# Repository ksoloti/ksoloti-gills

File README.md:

# ksoloti-gills
# CAD project and Gerbers for Ksoloti Gills v0.6

# Kicad 9.0!

## This is just the Gills unit (and CV expander) and will not work without a Ksoloti Core plugged in.

# Gills PCB
`Gerbers`, `BOM` and `CPL` files for the PCB are in the subfolder [/jlcpcb/production_files](https://github.com/ksoloti/ksoloti-gills/tree/main/jlcpcb/production_files)

Schematics are [here](https://github.com/ksoloti/ksoloti-gills/blob/main/ksoloti-gills_v06.pdf)

Human-readable BOM with notes and links is [here](https://github.com/ksoloti/ksoloti-gills/blob/main/ksoloti-gills_v06_bom.xlsx)

# Gills Enclosure Panels

`Gerbers` for the enclosure panels are in the subfolder [/ksoloti-gills_panel/jlcpcb/production_files](https://github.com/ksoloti/ksoloti-gills/tree/main/ksoloti-gills_panel/jlcpcb/production_files)
Although the Kicad project includes all panels, there is one gerber zip per panel: top, bottom, left, right, front, rear. If you have made edits and want to update the Gerbers, you will need to create separate Gerbers by pasting each relevant single panel in a temporary PCBNew window and `File->Plot...` it from there. Or so.
Note that there are two `ksoloti-gills-panel-top-*.zip`, one for black color, one for white. The silkscreens differ.

# Gills CV Expander PCB
`Gerbers`, `BOM` and `CPL` files for the CV Expander PCB are in the subfolder [/ksoloti-gills-cv-expander/jlcpcb/production_files](https://github.com/ksoloti/ksoloti-gills/tree/main/jlcpcb/production_files)

CV Expander Schematics are [here](https://github.com/ksoloti/ksoloti-gills/blob/main/ksoloti-gills-cv-expander/ksoloti-gills-cv-expander_v03.pdf)

BOM parts required for CV Expander are included in the main BOM (xlsx) above.

## About Licensing and Sharing 

This hardware design is shared under the "Creative Commons Attribution 4.0 International Public License" (CC BY 4.0).
This means you can use this design for almost anything, including commercial projects. You are totally free to reproduce, share, and modify it.

Because this is a physical hardware project, we ask for two small favours to keep the attribution clear:
- Keep the attribution text "CC BY 4.0 Ksoloti" on the silkscreen layer.
- If you make any significant edits and share your modified version, please note what modifications you've made. Do add something like "edit by <yourname>" if you like!

The full, official legal text is available in the `LICENSE` file in this repository. Happy hacking!

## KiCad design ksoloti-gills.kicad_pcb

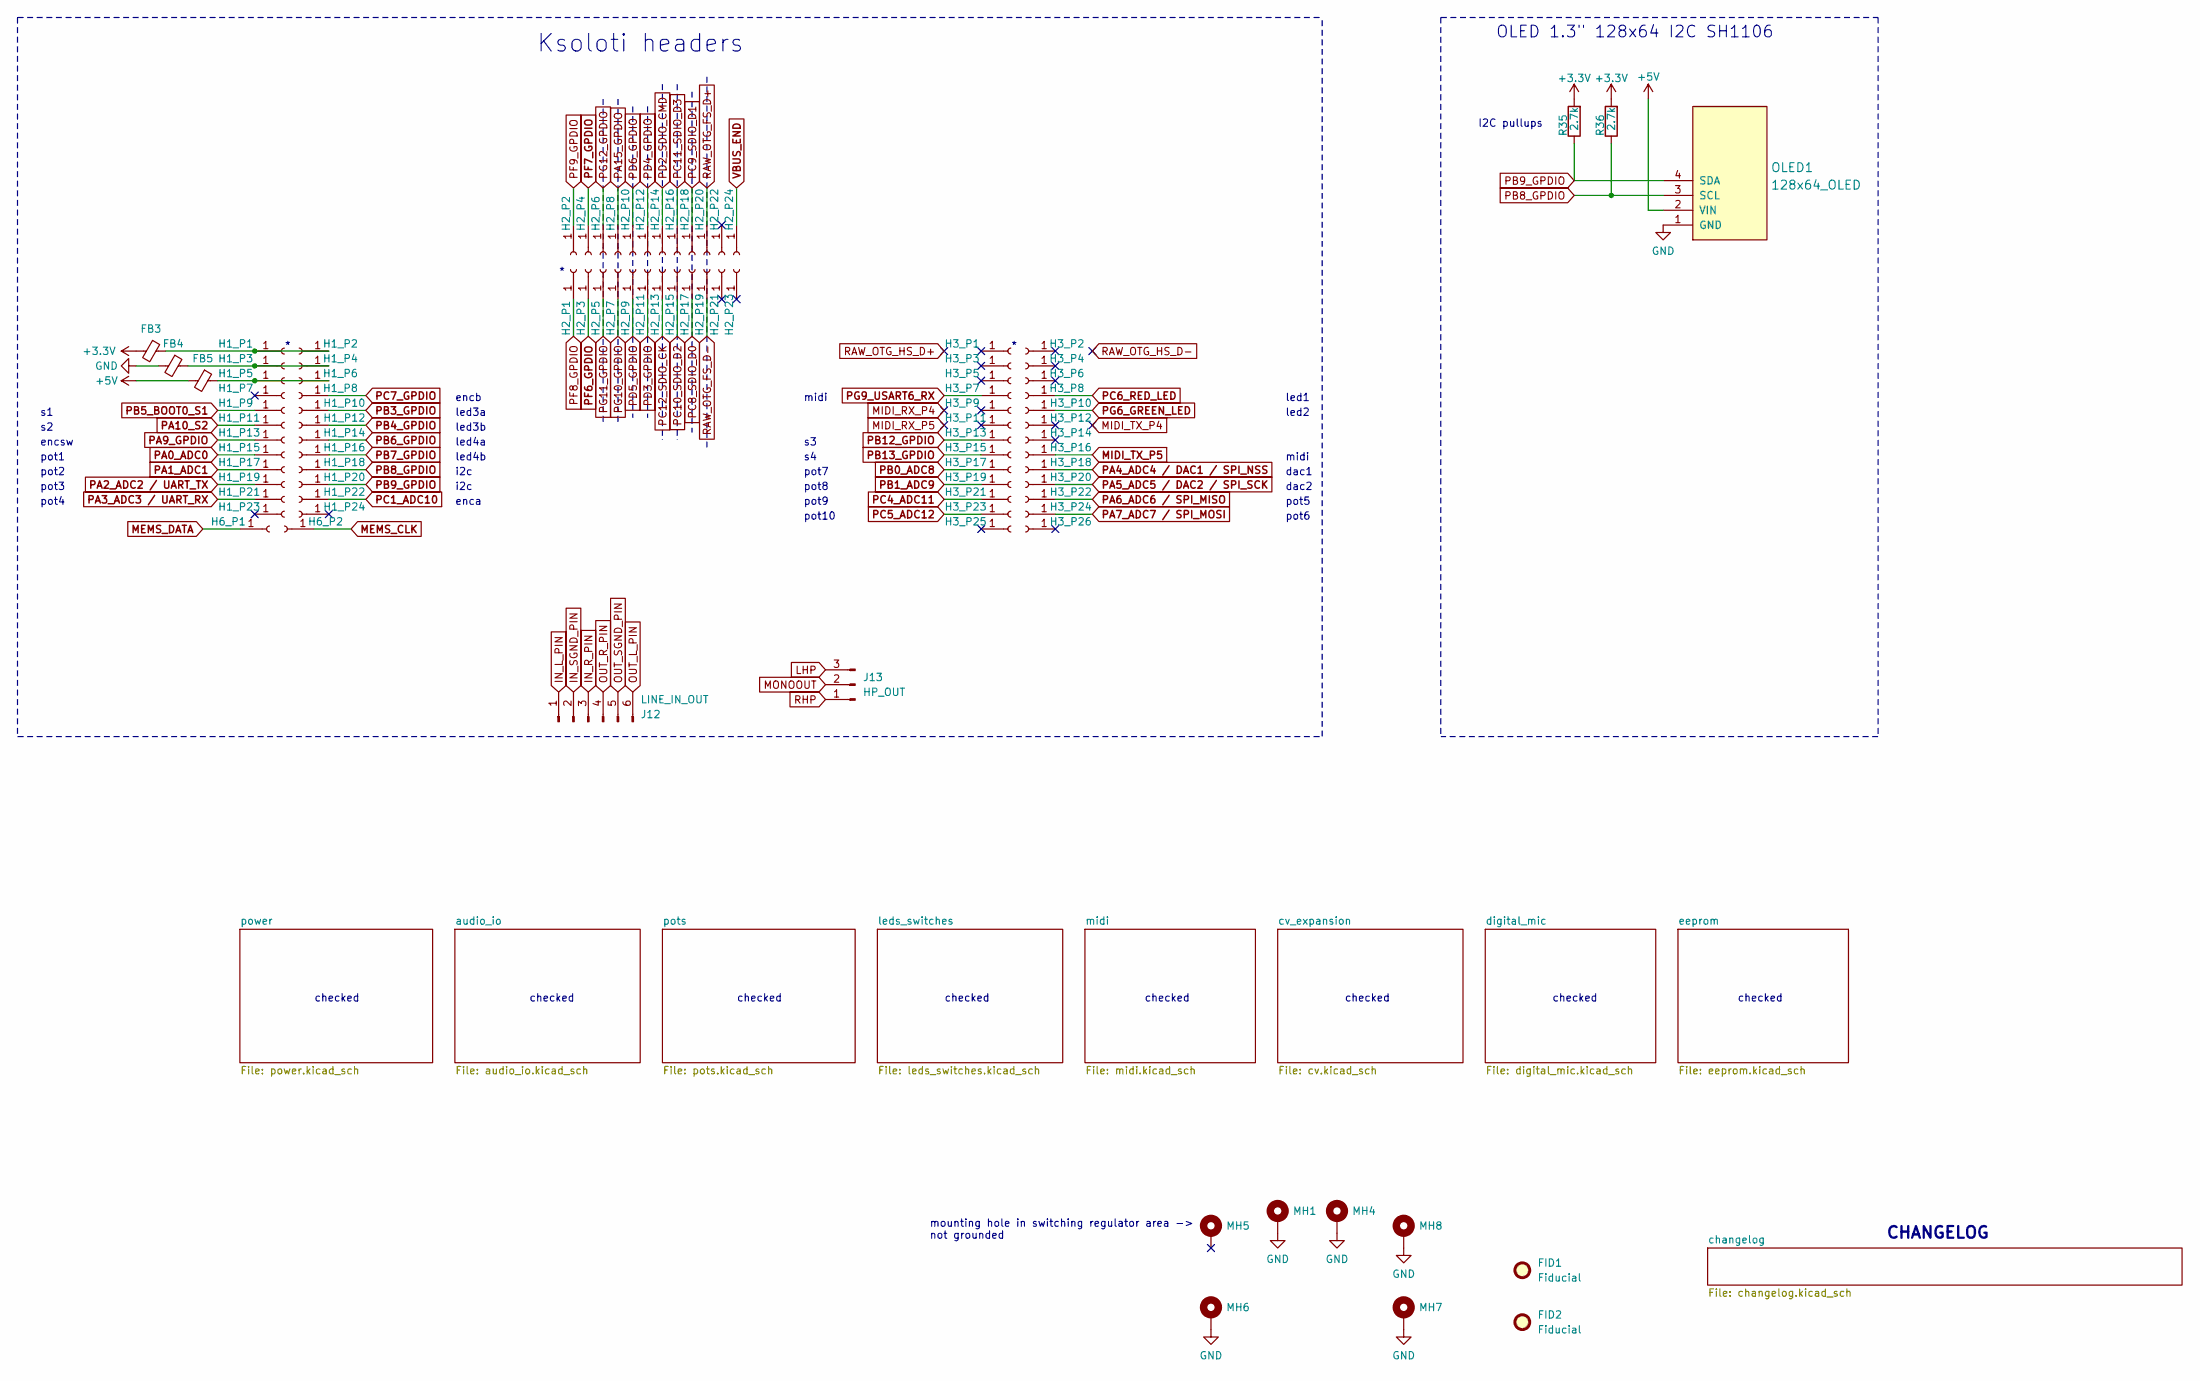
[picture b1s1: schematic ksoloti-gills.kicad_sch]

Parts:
FB3, FB4, FB5: 100 ohm @ 100 Mhz; R_1206_3216Metric
FID1, FID2: Fiducial; jlc_tooling_hole
H1_P1, H2_P1, H3_P1: Conn_01x01_Female; PinSocket_1x01_P2.54mm_Vertical_smcrt_sqr
H1_P2, H1_P3, H1_P4, H1_P5, H1_P6, H1_P7, H1_P8, H1_P9, H1_P10, H1_P11, H1_P12, H1_P13, H1_P14, H1_P15, H1_P16, H1_P17, H1_P18, H1_P19, H1_P20, H1_P21, H1_P22, H1_P23, H1_P24, H2_P2, H2_P3, H2_P4, H2_P21, H2_P22, H2_P23, H2_P24, H3_P2, H3_P3, H3_P4, H3_P5, H3_P6, H3_P7, H3_P8, H3_P9, H3_P10, H3_P11, H3_P12, H3_P13, H3_P14, H3_P15, H3_P16, H3_P17, H3_P18, H3_P19, H3_P20, H3_P21, H3_P22, H3_P23, H3_P24: Conn_01x01_Female; PinSocket_1x01_P2.54mm_Vertical_smcrt_round
H2_P5, H2_P6, H2_P7, H2_P8, H2_P9, H2_P10, H2_P11, H2_P12, H2_P13, H2_P14, H2_P15, H2_P16, H2_P17, H2_P18, H2_P19, H2_P20, H3_P25, H3_P26: Conn_01x01_Female; PinHeader_1x01_P2.54mm_Vertical_smcrt_round
H6_P1: DMIC_DAT; PinSocket_1x01_P2.54mm_Vertical_smcrt_round
H6_P2: DMIC_CLK; PinSocket_1x01_P2.54mm_Vertical_smcrt_round
J12: LINE_IN_OUT; PinSocket_1x06_P2.54mm_Vertical
J13: HP_OUT; PinSocket_1x03_P2.54mm_Vertical
MH1, MH4, MH5, MH6, MH7, MH8: MountingHole; MountingHole_3.2mm_M3_Pad_Via_tight
OLED1: 128x64_OLED; 128x64OLED_1_3in
R35, R36: 2.7k; R_0603_1608Metric

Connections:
+3.3V: FB3.2, R35.2, R36.2; also elsewhere on the board
+5V: FB5.2, OLED1.2 (VIN); also elsewhere on the board
GND: FB4.2, MH1.1, MH4.1, MH6.1, MH7.1, MH8.1, OLED1.1 (GND); also elsewhere on the board
IN_L_PIN: J12.1; also elsewhere on the board
IN_R_PIN: J12.3; also elsewhere on the board
IN_SGND_PIN: J12.2; also elsewhere on the board
LHP: J13.3; also elsewhere on the board
MEMS_CLK: H6_P2.1; also elsewhere on the board
MEMS_DATA: H6_P1.1; also elsewhere on the board
MIDI_TX_P5: H3_P16.1; also elsewhere on the board
MONOOUT: J13.2; also elsewhere on the board
unnamed: FB3.1, H1_P1.1, H1_P2.1
unnamed: FB4.1, H1_P3.1, H1_P4.1
unnamed: FB5.1, H1_P5.1, H1_P6.1
OUT_L_PIN: J12.6; also elsewhere on the board
OUT_R_PIN: J12.4; also elsewhere on the board
OUT_SGND_PIN: J12.5; also elsewhere on the board
PA0_ADC0: H1_P15.1; also elsewhere on the board
PA1_ADC1: H1_P17.1; also elsewhere on the board
PA2_ADC2 / UART_TX: H1_P19.1; also elsewhere on the board
PA3_ADC3 / UART_RX: H1_P21.1; also elsewhere on the board
PA4_ADC4 / DAC1 / SPI_NSS: H3_P18.1; also elsewhere on the board
PA5_ADC5 / DAC2 / SPI_SCK: H3_P20.1; also elsewhere on the board
PA6_ADC6 / SPI_MISO: H3_P22.1; also elsewhere on the board
PA7_ADC7 / SPI_MOSI: H3_P24.1; also elsewhere on the board
PA9_GPDIO: H1_P13.1; also elsewhere on the board
PA10_S2: H1_P11.1; also elsewhere on the board
PB0_ADC8: H3_P17.1; also elsewhere on the board
PB1_ADC9: H3_P19.1; also elsewhere on the board
PB3_GPDIO: H1_P10.1; also elsewhere on the board
PB4_GPDIO: H1_P12.1; also elsewhere on the board
PB5_BOOT0_S1: H1_P9.1; also elsewhere on the board
PB6_GPDIO: H1_P14.1; also elsewhere on the board
PB7_GPDIO: H1_P16.1; also elsewhere on the board
PB8_GPDIO: H1_P18.1, OLED1.3 (SCL), R36.1; also elsewhere on the board
PB9_GPDIO: H1_P20.1, OLED1.4 (SDA), R35.1; also elsewhere on the board
PB12_GPDIO: H3_P13.1; also elsewhere on the board
PB13_GPDIO: H3_P15.1; also elsewhere on the board
PC1_ADC10: H1_P22.1; also elsewhere on the board
PC4_ADC11: H3_P21.1; also elsewhere on the board
PC5_ADC12: H3_P23.1; also elsewhere on the board
PC6_RED_LED: H3_P8.1; also elsewhere on the board
PC7_GPDIO: H1_P8.1; also elsewhere on the board
PF6_GPDIO: H2_P3.1; also elsewhere on the board
PF7_GPDIO: H2_P4.1; also elsewhere on the board
PF8_GPDIO: H2_P1.1
PF9_GPDIO: H2_P2.1
PG6_GREEN_LED: H3_P10.1; also elsewhere on the board
PG9_USART6_RX: H3_P7.1; also elsewhere on the board
RHP: J13.1; also elsewhere on the board
VBUS_END: H2_P24.1; also elsewhere on the board

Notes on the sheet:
checked
dac2
i2c
led2
led3a
led3b
mounting hole in switching regulator area -> not grounded
led1
encb
pot10
encsw
midi
pot5
pot1
OLED 1.3" 128x64 I2C SH1106
pot8
I2C pullups
Ksoloti headers
pot2
CHANGELOG
led4b
pot7
led4a
pot6
enca
pot3
pot4
pot9
dac1

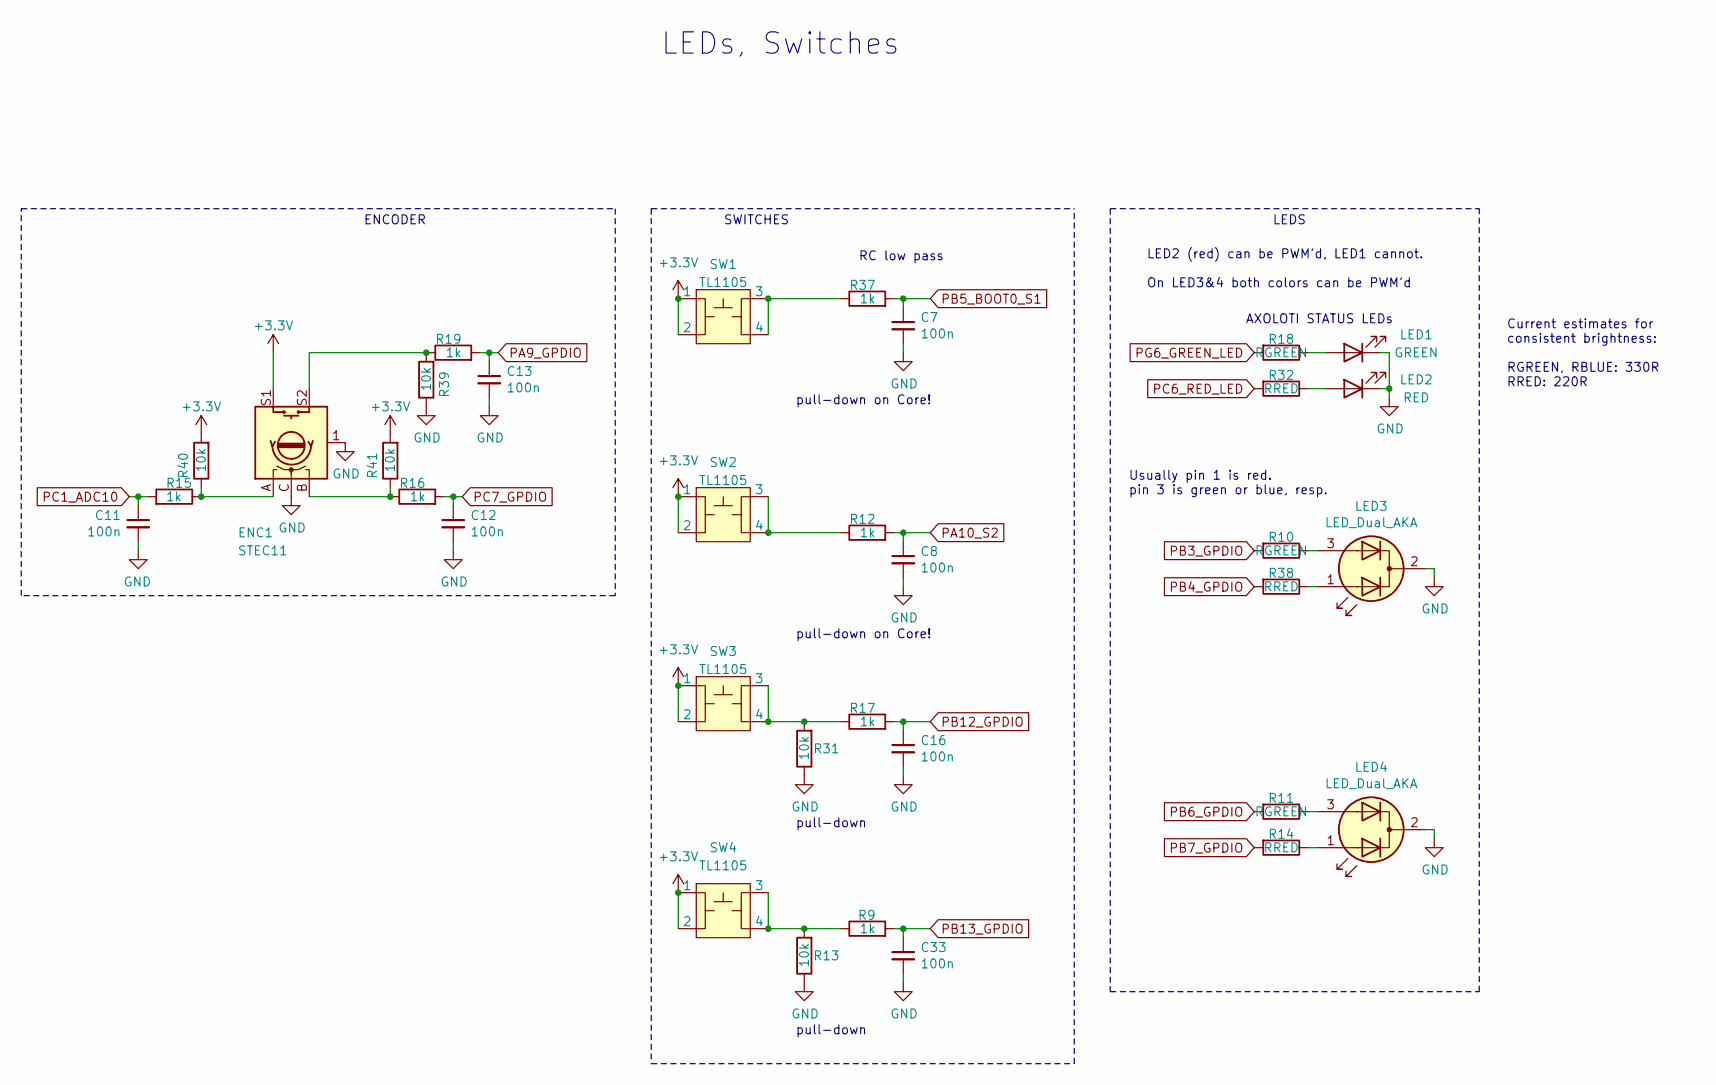
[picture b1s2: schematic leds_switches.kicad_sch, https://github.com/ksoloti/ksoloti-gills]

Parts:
C7, C8, C11, C12, C13, C16, C33: 100n; C_0603_1608Metric
ENC1: STEC11; ALPS_STEC12E08
LED1: GREEN; LED_D3.0mm_marked
LED2: RED; LED_D3.0mm_marked
LED3, LED4: LED_Dual_AKA; LED_D3.0mm-3_marked
R9, R12, R15, R16, R17, R19, R37: 1k; R_0603_1608Metric
R10, R11, R18: RGREEN; R_0805_2012Metric
R13, R31, R39, R40, R41: 10k; R_0603_1608Metric
R14, R32, R38: RRED; R_0805_2012Metric
SW1, SW2, SW3, SW4: TL1105; TL1105T

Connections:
+3.3V: ENC1.S1, R40.2, R41.2, SW1.1, SW1.2, SW2.1, SW2.2, SW3.1, SW3.2, SW4.1, SW4.2; also elsewhere on the board
GND: C7.2, C8.2, C11.2, C12.2, C13.2, C16.2, C33.2, ENC1.1, ENC1.C, LED1.1 (K), LED2.1 (K), LED3.2 (K), LED4.2 (K), R13.1, R31.1, R39.1; also elsewhere on the board
unnamed: ENC1.A, R15.1, R40.1
unnamed: ENC1.B, R16.1, R41.1
unnamed: ENC1.S2, R19.1, R39.2
unnamed: LED1.2 (A), R18.1
unnamed: LED2.2 (A), R32.1
unnamed: LED3.1 (A1), R38.1
unnamed: LED3.3 (A2), R10.1
unnamed: LED4.1 (A1), R14.1
unnamed: LED4.3 (A2), R11.1
unnamed: R12.1, SW2.3, SW2.4
unnamed: R9.1, R13.2, SW4.3, SW4.4
unnamed: R17.1, R31.2, SW3.3, SW3.4
unnamed: R37.1, SW1.3, SW1.4
PA9_GPDIO: C13.1, R19.2; also elsewhere on the board
PA10_S2: C8.1, R12.2; also elsewhere on the board
PB3_GPDIO: R10.2; also elsewhere on the board
PB4_GPDIO: R38.2; also elsewhere on the board
PB5_BOOT0_S1: C7.1, R37.2; also elsewhere on the board
PB6_GPDIO: R11.2; also elsewhere on the board
PB7_GPDIO: R14.2; also elsewhere on the board
PB12_GPDIO: C16.1, R17.2; also elsewhere on the board
PB13_GPDIO: C33.1, R9.2; also elsewhere on the board
PC1_ADC10: C11.1, R15.2; also elsewhere on the board
PC6_RED_LED: R32.2; also elsewhere on the board
PC7_GPDIO: C12.1, R16.2; also elsewhere on the board
PG6_GREEN_LED: R18.2; also elsewhere on the board

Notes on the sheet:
ENCODER
SWITCHES
pull-down on Core!
LEDS
LED2 (red) can be PWM'd, LED1 cannot. On LED3&4 both colors can be PWM'd
LEDs, Switches
Current estimates for consistent brightness: RGREEN, RBLUE: 330R RRED: 220R
Usually pin 1 is red. pin 3 is green or blue, resp.
pull-down
AXOLOTI STATUS LEDs
RC low pass

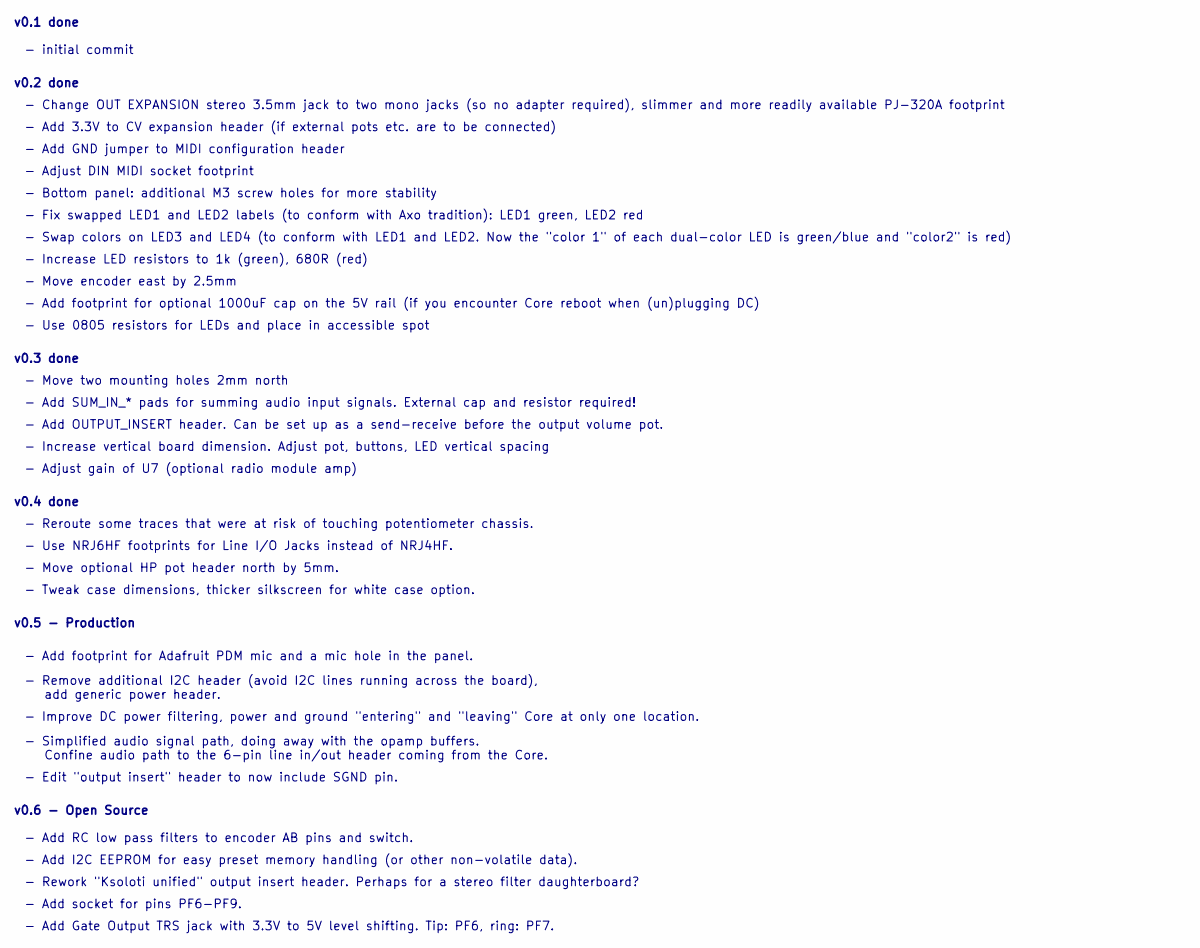
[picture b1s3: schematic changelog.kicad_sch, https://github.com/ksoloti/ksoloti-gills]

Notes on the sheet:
- Rework "Ksoloti unified" output insert header. Perhaps for a stereo filter daughterboard?
- Use NRJ6HF footprints for Line I/O Jacks instead of NRJ4HF.
- initial commit
v0.5 - Production
v0.2 done
- Tweak case dimensions, thicker silkscreen for white case option.
- Change OUT EXPANSION stereo 3.5mm jack to two mono jacks (so no adapter required), slimmer and more readily available PJ-320A footprint
- Add I2C EEPROM for easy preset memory handling (or other non-volatile data).
- Move encoder east by 2.5mm
- Move optional HP pot header north by 5mm.
- Add footprint for Adafruit PDM mic and a mic hole in the panel.
- Add Gate Output TRS jack with 3.3V to 5V level shifting. Tip: PF6, ring: PF7.
- Add GND jumper to MIDI configuration header
- Remove additional I2C header (avoid I2C lines running across the board), add generic power header.
- Increase vertical board dimension. Adjust pot, buttons, LED vertical spacing
- Move two mounting holes 2mm north
- Fix swapped LED1 and LED2 labels (to conform with Axo tradition): LED1 green, LED2 red
- Adjust DIN MIDI socket footprint
- Add footprint for optional 1000uF cap on the 5V rail (if you encounter Core reboot when (un)plugging DC)
- Add socket for pins PF6-PF9.
v0.6 - Open Source
- Edit "output insert" header to now include SGND pin.
- Simplified audio signal path, doing away with the opamp buffers. Confine audio path to the 6-pin line in/out header coming from the Core.
- Increase LED resistors to 1k (green), 680R (red)
- Swap colors on LED3 and LED4 (to conform with LED1 and LED2. Now the "color 1" of each dual-color LED is green/blue and "color2" is red)
- Improve DC power filtering, power and ground "entering" and "leaving" Core at only one location.
v0.4 done
v0.1 done
- Add SUM_IN_* pads for summing audio input signals. External cap and resistor required!
- Adjust gain of U7 (optional radio module amp)
v0.3 done
- Bottom panel: additional M3 screw holes for more stability
- Add 3.3V to CV expansion header (if external pots etc. are to be connected)
- Add OUTPUT_INSERT header. Can be set up as a send-receive before the output volume pot.
- Reroute some traces that were at risk of touching potentiometer chassis.
- Use 0805 resistors for LEDs and place in accessible spot
- Add RC low pass filters to encoder AB pins and switch.

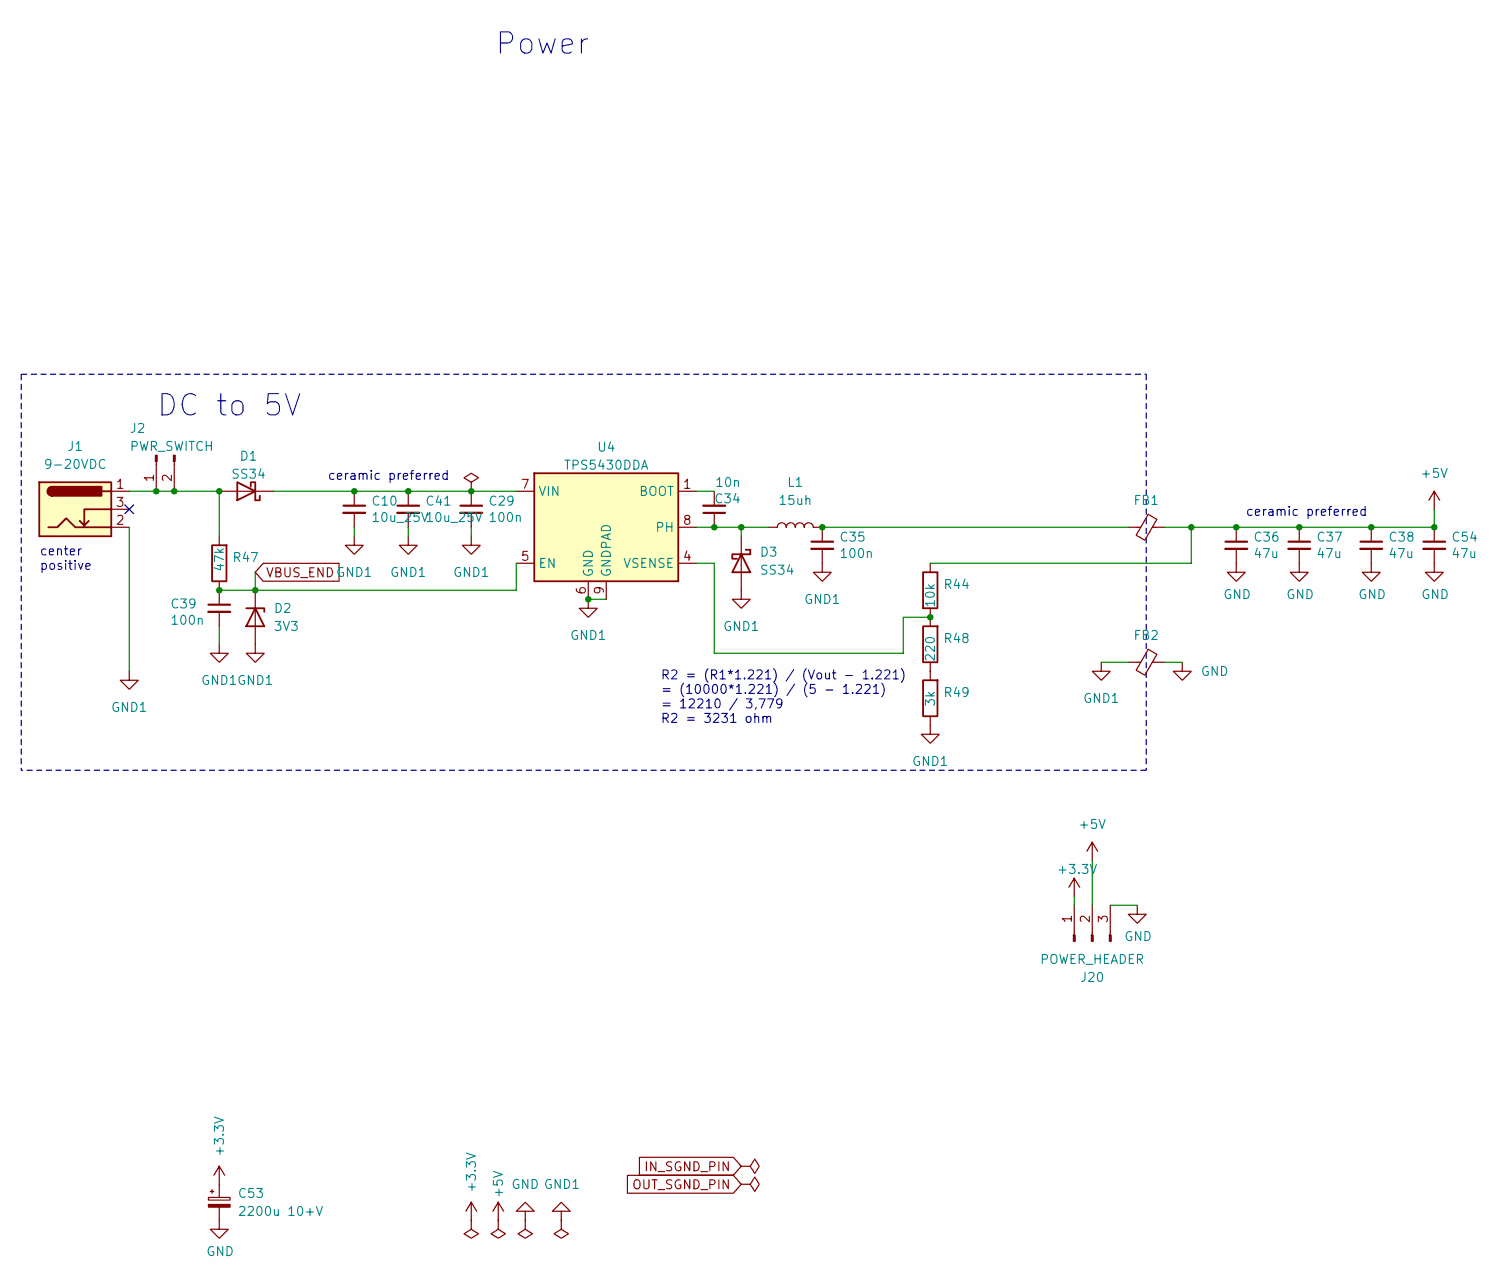
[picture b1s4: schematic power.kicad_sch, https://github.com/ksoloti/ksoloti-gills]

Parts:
C10, C41: 10u_25V; C_0603_1608Metric
C29, C35, C39: 100n; C_0603_1608Metric
C34: 10n; C_0603_1608Metric
C36, C37, C38, C54: 47u; C_1206_3216Metric
C53: 2200u 10+V; CP_Radial_D10.0mm_P5.00mm
D1, D3: SS34; D_SMA
D2: 3V3; D_MiniMELF
FB1, FB2: 100 ohm @ 100 Mhz; R_1206_3216Metric
J1: 9-20VDC; dc_socket
J2: PWR_SWITCH; PinHeader_1x02_P2.54mm_Vertical
J20: POWER_HEADER; PinHeader_1x03_P2.54mm_Vertical
L1: 15uh; L_7.3x6.7_H3.5
R44: 10k; R_0603_1608Metric
R47: 47k; R_0603_1608Metric
R48: 220; R_0603_1608Metric
R49: 3k; R_0603_1608Metric
U4: TPS5430DDA; TI_SO-PowerPAD-8_ThermalVias

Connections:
+3.3V: C53.1, J20.1; also elsewhere on the board
+5V: C36.1, C37.1, C38.1, C54.1, FB1.1, J20.2, R44.1; also elsewhere on the board
GND: C36.2, C37.2, C38.2, C53.2, C54.2, FB2.1, J20.3; also elsewhere on the board
GND1: C10.2, C29.2, C35.2, C39.2, C41.2, D2.2 (A), D3.2 (A), FB2.2, J1.2, R49.1, U4.6 (GND), U4.9 (GNDPAD)
unnamed: C35.1, FB1.2, L1.2
unnamed: D1.2 (A), J1.1, J2.1, J2.2, R47.2
unnamed: C10.1, C29.1, C41.1, D1.1 (K), U4.7 (VIN)
unnamed: C34.1, D3.1 (K), L1.1, U4.8 (PH)
unnamed: R48.1, R49.2
unnamed: C34.2, U4.1 (BOOT)
unnamed: R44.2, R48.2, U4.4 (VSENSE)
VBUS_END: C39.1, D2.1 (K), R47.1, U4.5 (EN); also elsewhere on the board

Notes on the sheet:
Power
DC to 5V
center positive
ceramic preferred
R2 = (R1*1.221) / (Vout - 1.221) = (10000*1.221) / (5 - 1.221) = 12210 / 3,779 R2 = 3231 ohm

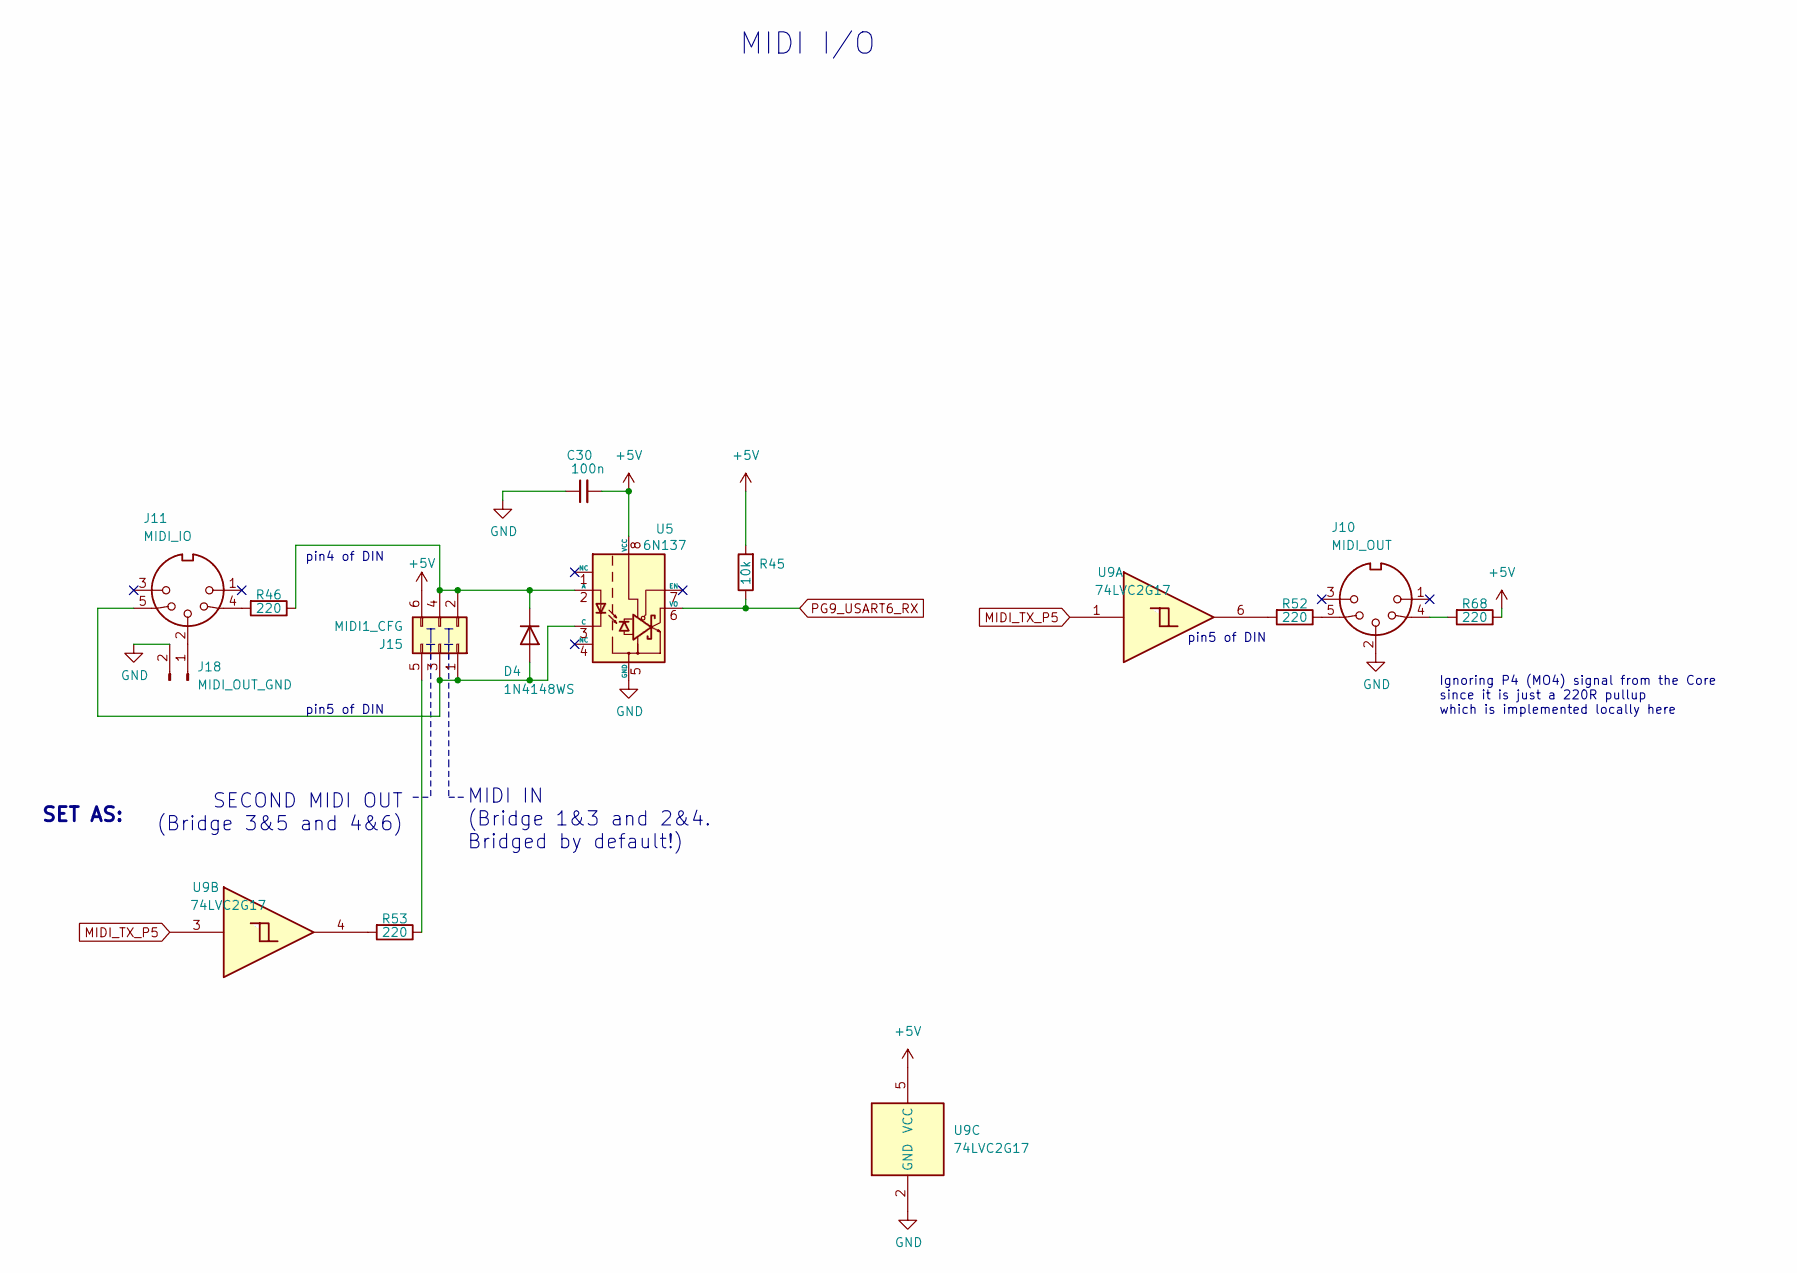
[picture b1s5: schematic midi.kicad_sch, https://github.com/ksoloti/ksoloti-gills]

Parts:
C30: 100n; C_0603_1608Metric
D4: 1N4148WS; D_SOD-323
J10: MIDI_OUT; MIDI_DIN-5_DS-5-01c
J11: MIDI_IO; MIDI_DIN-5_DS-5-01c
J15: MIDI1_CFG; PinHeader_2x03_P2.54mm_Vertical
J18: MIDI_OUT_GND; PinHeader_1x02_P2.54mm_Vertical
R45: 10k; R_0603_1608Metric
R46, R52, R53, R68: 220; R_0603_1608Metric
U5: 6N137; SMDIP-8_W9.53mm
U9: 74LVC2G17; SOT-23-6

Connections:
+5V: C30.2, J15.6, R45.2, R68.1, U5.8 (VCC), U9.5 (VCC); also elsewhere on the board
GND: C30.1, J10.2, J18.2, U5.5 (GND), U9.2 (GND); also elsewhere on the board
MIDI_TX_P5: U9.1, U9.3; also elsewhere on the board
unnamed: D4.2 (A), J11.5, J15.1, J15.3, U5.3 (C)
unnamed: D4.1 (K), J15.2, J15.4, R46.1, U5.2 (A)
unnamed: J10.4, R68.2
unnamed: J10.5, R52.1
unnamed: J11.4, R46.2
unnamed: J15.5, R53.1
unnamed: J11.2, J18.1
unnamed: R52.2, U9.6
unnamed: R53.2, U9.4
PG9_USART6_RX: R45.1, U5.6 (VO); also elsewhere on the board

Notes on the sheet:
Ignoring P4 (MO4) signal from the Core since it is just a 220R pullup which is implemented locally here
MIDI IN (Bridge 1&3 and 2&4. Bridged by default!)
pin4 of DIN
pin5 of DIN
MIDI I/O
SECOND MIDI OUT (Bridge 3&5 and 4&6)
SET AS:

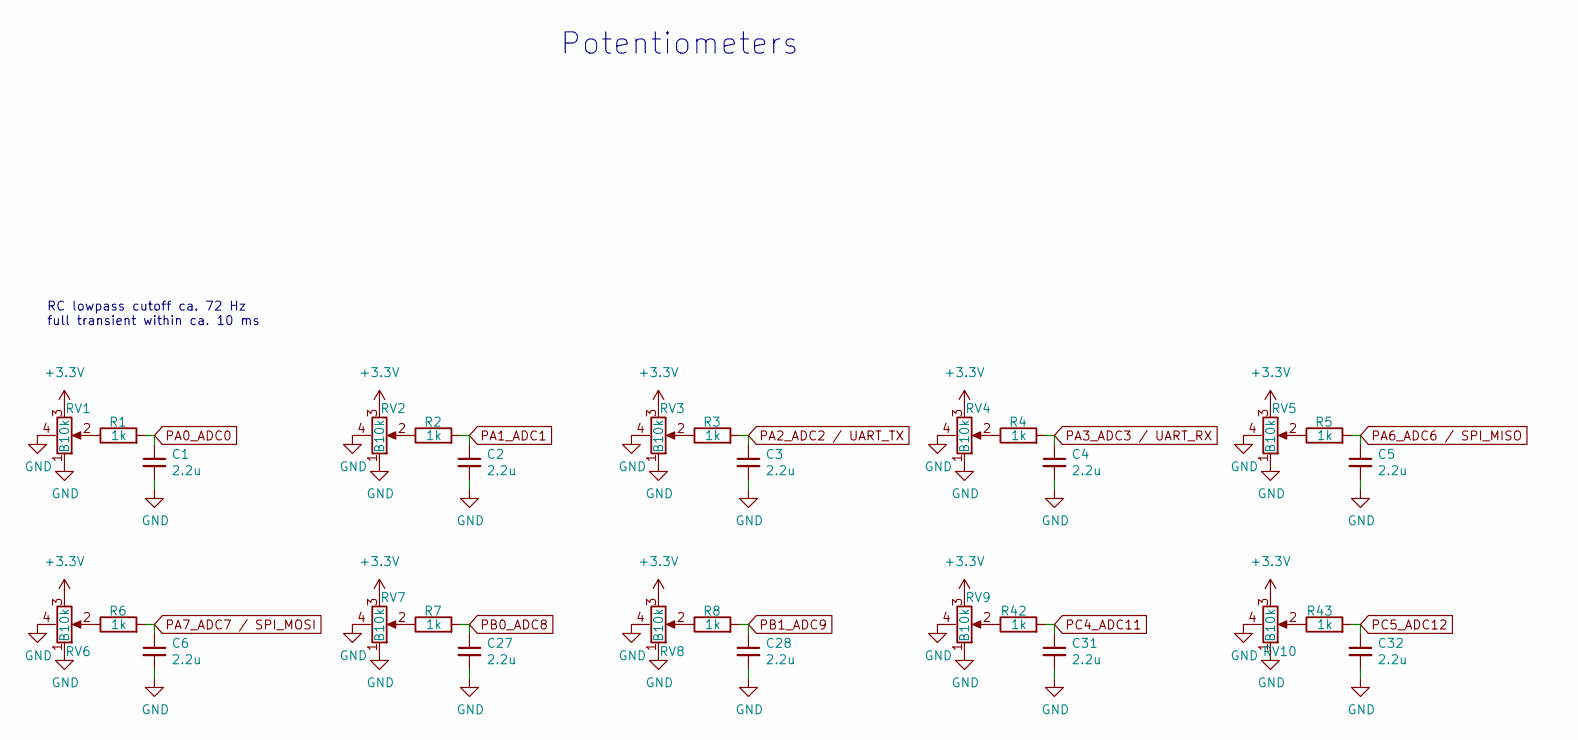
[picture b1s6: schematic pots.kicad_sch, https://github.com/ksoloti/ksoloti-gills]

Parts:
C1, C2, C3, C4, C5, C6, C27, C28, C31, C32: 2.2u; C_0603_1608Metric
R1, R2, R3, R4, R5, R6, R7, R8, R42, R43: 1k; R_0603_1608Metric
RV1, RV2, RV3, RV4, RV5, RV6, RV7, RV8, RV9, RV10: B10k; ALPS_POT_VERTICAL_PS

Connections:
+3.3V: RV1.3, RV2.3, RV3.3, RV4.3, RV5.3, RV6.3, RV7.3, RV8.3, RV9.3, RV10.3; also elsewhere on the board
GND: C1.2, C2.2, C3.2, C4.2, C5.2, C6.2, C27.2, C28.2, C31.2, C32.2, RV1.1, RV1.4, RV2.1, RV2.4, RV3.1, RV3.4, RV4.1, RV4.4, RV5.1, RV5.4, RV6.1, RV6.4, RV7.1, RV7.4, RV8.1, RV8.4, RV9.1, RV9.4, RV10.1, RV10.4; also elsewhere on the board
unnamed: R1.1, RV1.2
unnamed: R2.1, RV2.2
unnamed: R3.1, RV3.2
unnamed: R4.1, RV4.2
unnamed: R5.1, RV5.2
unnamed: R6.1, RV6.2
unnamed: R7.1, RV7.2
unnamed: R8.1, RV8.2
unnamed: R42.1, RV9.2
unnamed: R43.1, RV10.2
PA0_ADC0: C1.1, R1.2; also elsewhere on the board
PA1_ADC1: C2.1, R2.2; also elsewhere on the board
PA2_ADC2 / UART_TX: C3.1, R3.2; also elsewhere on the board
PA3_ADC3 / UART_RX: C4.1, R4.2; also elsewhere on the board
PA6_ADC6 / SPI_MISO: C5.1, R5.2; also elsewhere on the board
PA7_ADC7 / SPI_MOSI: C6.1, R6.2; also elsewhere on the board
PB0_ADC8: C27.1, R7.2; also elsewhere on the board
PB1_ADC9: C28.1, R8.2; also elsewhere on the board
PC4_ADC11: C31.1, R42.2; also elsewhere on the board
PC5_ADC12: C32.1, R43.2; also elsewhere on the board

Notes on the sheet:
Potentiometers
RC lowpass cutoff ca. 72 Hz full transient within ca. 10 ms

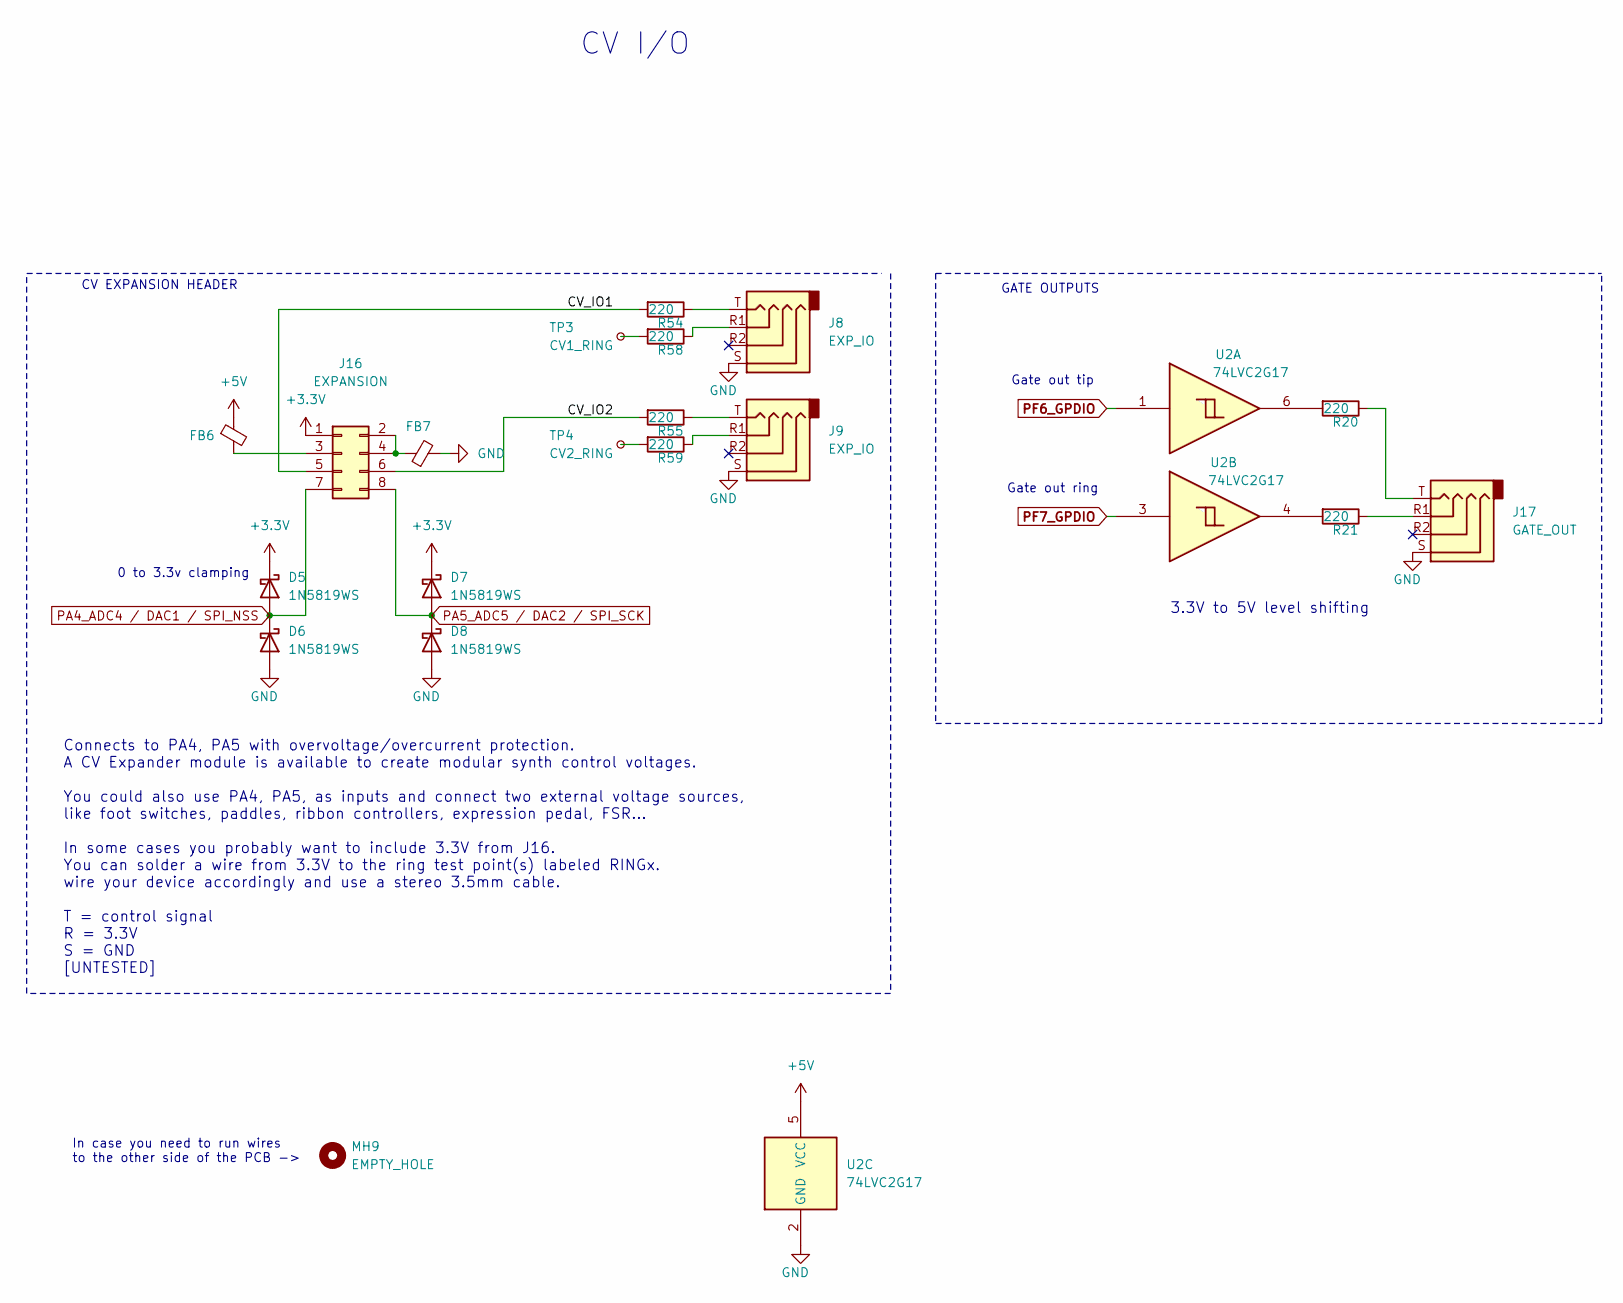
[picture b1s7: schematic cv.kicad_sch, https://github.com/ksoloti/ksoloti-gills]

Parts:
D5, D6, D7, D8: 1N5819WS; D_SOD-323
FB6, FB7: 100 ohm @ 100 Mhz; R_0805_2012Metric
J8, J9: EXP_IO; PJ-320A_THT
J16: EXPANSION; PinHeader_2x04_P2.54mm_Vertical
J17: GATE_OUT; PJ-320A_THT
MH9: EMPTY_HOLE; MountingHole_6mm
R20, R21, R54, R55, R58, R59: 220; R_0603_1608Metric
TP3: CV1_RING; TestPoint_THTPad_D1.5mm_Drill0.7mm
TP4: CV2_RING; TestPoint_THTPad_D1.5mm_Drill0.7mm
U2: 74LVC2G17; SOT-23-6

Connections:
+3.3V: D5.1 (K), D7.1 (K), J16.1; also elsewhere on the board
+5V: FB6.1, U2.5 (VCC); also elsewhere on the board
/cv_expansion/CV_IO1: J16.5, R54.2
/cv_expansion/CV_IO2: J16.6, R55.2
GND: D6.2 (A), D8.2 (A), FB7.2, J8.S, J9.S, J17.S, U2.2 (GND); also elsewhere on the board
unnamed: J8.R1, R58.1
unnamed: J8.T, R54.1
unnamed: J9.R1, R59.1
unnamed: J9.T, R55.1
unnamed: FB7.1, J16.2, J16.4
unnamed: FB6.2, J16.3
unnamed: J17.R1, R21.1
unnamed: J17.T, R20.1
unnamed: R20.2, U2.6
unnamed: R21.2, U2.4
unnamed: R58.2, TP3.1
unnamed: R59.2, TP4.1
PA4_ADC4 / DAC1 / SPI_NSS: D5.2 (A), D6.1 (K), J16.7; also elsewhere on the board
PA5_ADC5 / DAC2 / SPI_SCK: D7.2 (A), D8.1 (K), J16.8; also elsewhere on the board
PF6_GPDIO: U2.1; also elsewhere on the board
PF7_GPDIO: U2.3; also elsewhere on the board

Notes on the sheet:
In case you need to run wires to the other side of the PCB ->
CV I/O
0 to 3.3v clamping
3.3V to 5V level shifting
GATE OUTPUTS
Connects to PA4, PA5 with overvoltage/overcurrent protection. A CV Expander module is available to create modular synth control voltages. You could also use PA4, PA5, as inputs and connect two external voltage sources, like foot switches, paddles, ribbon controllers, expression pedal, FSR... In som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
Gate out tip
Gate out ring
CV EXPANSION HEADER

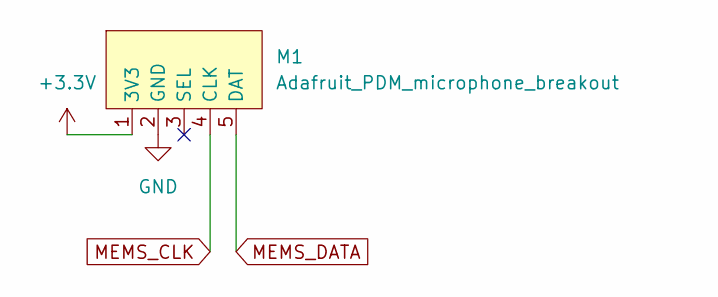
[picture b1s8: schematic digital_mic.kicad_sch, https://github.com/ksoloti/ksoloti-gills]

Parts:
M1: Adafruit_PDM_microphone_breakout; Adafruit PDM microphone breakout

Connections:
+3.3V: M1.1 (3V3); also elsewhere on the board
GND: M1.2 (GND); also elsewhere on the board
MEMS_CLK: M1.4 (CLK); also elsewhere on the board
MEMS_DATA: M1.5 (DAT); also elsewhere on the board
